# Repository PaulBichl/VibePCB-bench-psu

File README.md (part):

# vibepcb-bench-psu

USB-C PD (20 V) powered bench supply, 2 independent channels, 1.6-16.6 V / 3 A each, constant voltage / constant
current, designed with [VibePCB](../VibePCB). Board: `boards/bench-psu` (rev C: 90 x 60 mm, 4 layers, parts on both
sides). Design rationale is also in the header of `boards/bench-psu/index.circuit.tsx`.

The board is the front panel: the top carries what a user touches (0.96" OLED module, per channel an encoder and an
ON/OFF button, ON / CC LEDs, the output terminal), the bottom carries all electronics.

```
USB-C PD (STUSB4500, 20 V) -> P-FET -> VIN
   VIN -> 5 V buck (LMR33630) -> 3.3 V LDO -> ESP32-S3-MINI-1 (I2C, PWM, PCNT, ADC, BLE, native USB)
   VIN -> LMR33630 buck (x2) -> 20 mR shunt (INA226 + INA181) -> output terminal (CH1, CH2)
ESP32 PWM -> RC -> op-amp/NPN current sink on FB            = voltage set point (CV)
ESP32 PWM -> RC -> differential PI integrator -> diode -> FB = current limit (CC), vs INA181 (1 V/A)
INA226 ALERT -> buck EN = hardware over-current trip (backstop)
per channel: EC11 encoder (turn: set, push: V <-> I), ON/OFF button, ON LED (= EN), CC LED (GPIO),
             output discharge (2N7002 + 4.7k while off), SS54 reverse diode, FB clamp, NTC on the converter
USB D+/D-: 90 Ohm pair on the top layer (USBLC6 -> ESP32)
J3: SSD1306 0.96" I2C OLED module (bought separately, see "Parts bought separately")
```

## Look at it (`boards/bench-psu/hardware/`)

| What | File |
|------|------|
| Schematic | [bench-psu-schematic.pdf](boards/bench-psu/hardware/bench-psu-schematic.pdf) |
| Top view (3D) | [bench-psu-top.png](boards/bench-psu/hardware/bench-psu-top.png) |
| Bottom view (3D) | [bench-psu-bottom.png](boards/bench-psu/hardware/bench-psu-bottom.png) |
| Layout | [front](boards/bench-psu/hardware/bench-psu-layout-front.svg), [back](boards/bench-psu/hardware/bench-psu-layout-back.svg), [PDF](boards/bench-psu/hardware/bench-psu-layout.pdf) |
| KiCad project (open the `.kicad_pro`) | [kicad/](boards/bench-psu/hardware/kicad/) |
| BOM (JLCPCB format, LCSC + MPN) | [bench-psu-bom.csv](boards/bench-psu/hardware/bench-psu-bom.csv) |

Fab files (Gerbers + drill, BOM, CPL, bring-up sheet, firmware pin header) are generated, not committed:
`hatch run pcb fab bench-psu` writes them to `out/bench-psu/fab/` (it refuses unless `check --strict` passes).

## Design decisions

- **Parts:** everything in LCSC stock (checked 2026-10-25 with `hatch run pcb cost bench-psu`); basic-library passives
  wherever the value exists. Two-sided assembly: all SMD on the bottom except the status LEDs and their drivers;
  the front-panel parts (encoders, buttons, OLED header, terminal) are through-hole and hand-soldered.
- **Form factor:** 90 x 60 mm: the front-panel parts are through-hole, so their pins also take
  room on the bottom; 90 mm is what the two channel blocks, the control columns and the ESP32 need side by side.
  4 x M3 holes at (+-41.5, +-26.5) mm from the centre, keepouts for screw heads in `vibepcb.toml`.
- **Plain buck, not buck-boost:** the PD input (20 V) is always above the output (max 16.6 V).
- **Converter:** LMR33630A per channel (synchronous, 3 A, 400 kHz, HSOIC-8 with exposed pad, 36 V input),
  15 uH / 7 A sat FXL1040-150 inductor (TI's L_MIN is 11.6 uH at 16.6 V / 400 kHz), 4 x 22 uF/25 V ceramic output +
  100 uF electrolytic at the terminal (C25 / C26: the ceramics derate to ~18 uF at 16 V while the loop gain stays the
  same), 2 x 10 uF/50 V + 220 nF/50 V input.
  **Thermal vias** (2 x 3, 0.3 mm, `[thermal_vias.*]`) in every LMR33630 exposed pad; the pad connects solid to the
  pours.
- **Voltage setting, fail-safe:** an op-amp (TLV9062) + NPN sinks Ic = Vc / 2.2k from the feedback node,
  Vc = PWM (14-bit, 2-pole RC) * 10k/120k (R106 + R107 + R108): Vout = 1.6 V + 4.55 * Vpwm, i.e. 1.6 V at 0 V / floating PWM or MCU reset,
  16.6 V at 3.3 V PWM (the hardware maximum), ~0.9 mV per step. Feedback is taken at the terminal, after the shunt.
  Firmware closes the loop on the INA226 bus-voltage reading.
- **Loop compensation:** the FB network has a feedback gain of 0.625 at every output voltage, but the LMR33630's
  internal compensation expects 1 V / Vout: unstable without help. 6.8k + 220 nF from FB to GND (lag network) lowers
  the gain above ~100 Hz: phase margin 93-98 deg, crossover 9-38 kHz (simulated; see the open point on the lowest
  phase below crossover in "Status").
- **FB clamp (rev C, from the review):** the buck can't pull its output down, so after a set-point drop or a lost PWM
  (MCU reset) FB would sit at 0.625 x OUT, up to 10.4 V against a 5.5 V absolute maximum, for seconds. A 1N4148W per
  channel (D16 / D26, FB -> 3V3) holds it at ~3.8 V (`sim/powerup_ch.cir`); in operation it is reverse-biased (nA).
- **Start-up:** the lag capacitor is pre-charged to ~1.3 V while the channel is off (1N4148W + 100k from the
  discharge-gate node); otherwise the soft start charges it through the 120k top resistor and every enable overshoots
  to ~7.7 V. With EN high the diode blocks: no offset. Overshoot 0.02 % (`sim/powerup_ch.cir`).
- **Constant current:** INA181A2 (x50) on the shunt = 1 V/A; ISET = PWM, 2-pole RC, 1 V/A; a TLV9062 half as a
  differential PI integrator (10k, 330 R + 100 nF in both legs) sources current into FB through 10k + 1N4148W when
  I > Iset. Differential, because the plant gain into a short is ~240: a plain non-inverting PI keeps a
  high-frequency gain >= 1 and oscillates. Simulated phase margin >= 91 deg from a short to 5 R, a 20 R -> 2 R step
  settles in 1.7 ms (`sim/cc_loop.cir`). In CV the amp rests at 0 V, the diode is off. Into a hard short the
  converter may hiccup once before the loop holds (current limited either way).
- **Enable / current trip:** ESP32 drives each buck's EN through 10k (100k pull-down: off at reset). The INA226 ALERT
  (shunt over-limit, latched) pulls EN low directly: the hard backstop, at a ceiling the firmware sets above Iset.
- **Output:** 100 nF at the terminal (INA226 VBUS); SS54 reverse diode (a reversed source is clamped); active
  discharge while off (2N7002 + 4.7k, gate from 5 V, held off by an NPN while EN is high): "off" is below 0.5 V within
  ~2 s (~60 s through the divider alone), also at reset and after a trip.
- **Cooling: passive.** ~2-2.5 W per channel at 3 A (1.2-1.6 W in the IC, datasheet-maximum Rds(on)). With the thermal
  vias Tj stays below 112 C at 45 C ambient (35 C room + 10 K in a vented enclosure; ~160 C without vias,
  `sim/buck_loadpoints.cir`). A 10k NTC
  (Murata NCP18XH103F03RB) next to each converter feeds ESP32 ADC1 (IO1 / IO2) for firmware derating; the converter's
  thermal shutdown is the last resort. No fan.
- **Measurement:** INA226 per channel (0x40 CH1, 0x41 CH2), 20 mR shunt: 4.096 A full scale, 125 uA / 1.25 mV LSB,
  60 mV drop and 0.18 W at 3 A.
- **Input protection:** ESDA25P35 TVS on VBUS at the connector (ahead of Q1: the STUSB4500's VDD is rated 28 V),
  ESDA25W ESD array on CC1 / CC2 as in ST's reference; D+/D- through the USBLC6. The connector shell goes to GND
  through 1 MOhm || 4.7 nF rated 1 kV (an 8 kV / 150 pF shell discharge charges it to ~250 V).
- **USB data:** D+/D- run from the USBLC6 to the ESP32 as a coupled pair on the top layer over the In1 GND plane,
  0.32 / 0.2 mm = 90 Ohm differential (JLC04161H-7628 stack-up), two vias per line; drawn as a fixed path in the TSX
  (tscircuit's router does not couple pairs). Full Speed USB would work uncoupled too; this is the standard layout.
- **Input:** STUSB4500 drives the AO4407A gate through 47k against 100k gate-source (Vgs stays inside +-25 V up to the
  TVS clamp), 100 nF gate-source for a slow turn-on. SMBJ22A TVS (35.5 V clamp, below the LMR33630's 38 V abs max),
  100 uF SMD electrolytic for damping.
- **Logic supply:** 5 V buck (same LMR33630, 6.8 uH / 4 A sat FXL0530, 4 x 22 uF output, two of them on the top side)
  -> AP2112K 3.3 V; native USB on the ESP32 for flashing / CDC.
- **Front panel:** EC11E15244B2 encoders (counted by the S3's PCNT units), Omron B3F-4055 12 mm buttons (wired on
  diagonal pads 1 / 4: always across the contact), 3.3k pull-up + 33 nF on every front-panel line (1 mA contact
  current, the EC11's minimum for contact wetting). 0.96" SSD1306
  I2C module (0x3C) on J3, its content is firmware.
- **Status LEDs:** ON (yellow-green) follows the converter's EN node through an NPN (hardware truth, dark after an
  INA226 trip); CC (red) is a GPIO (IO21 / IO47) the firmware lights while the channel is current-limited.
- **Antenna:** the ESP32-S3-MINI-1 (bottom) points its antenna at the +x board edge; no copper under it on any layer.

## History

Rev A (first draft) used a TSOT-23 converter at 1.1 MHz, injected the PWM straight into FB (0 V PWM = 18 V out) and had
no hardware current trip. Rev B moved to the LMR33630 with the fail-safe current-sink voltage setting, the INA226 trip
and the FB lag network. Rev C (this board):

| rev B | rev C | why |
|-------|-------|-----|
| 90 x 76 mm, everything on top | 90 x 60 mm, front panel on top, electronics on the bottom | the board is the front panel; smaller |
| OLED + KY-040 encoder as modules on headers | OLED module on J3, per channel EC11 encoder + ON/OFF button on the board | per-channel controls |
| current trip only (INA226 ALERT -> EN) | CC loop (INA181 + differential PI into FB) + the trip as backstop | a real current limit instead of switching off |
| lag capacitor starts discharged | pre-charged while off (1N4148W + 100k) | 7.7 V overshoot at every enable (simulated) |
| output decays over ~28 s when off | 2N7002 + 4.7k discharge while EN is low | "off" means 0 V |
| no reverse protection | SS54 across each output | reversed source / battery clamped |
| no thermal vias | 2 x 3 via grid in each exposed pad | Tj ~160 C -> 112 C at 45 C ambient, 3 A |
| no temperature sensing, no mounting holes | NTC per converter on ADC1, 4 x M3 | firmware derating with passive cooling; enclosure |
| sim decks run by hand | 5 decks run by `check`, pass ranges with sources | verification is enforced |
| 2.4k sink resistor: Vout_max 15.2 V | 2.2k: 16.6 V | review: R106 in series with the VSET divider |
| 10 uH channel / 15 uH (1.65 A sat) logic inductors | 15 uH / 7 A sat, 6.8 uH / 4 A sat | below TI's L_MIN; saturating below the current limit (review) |
| no TVS / ESD at the USB-C input, 50 V shell cap | ESDA25P35 on VBUS, ESDA25W on CC, 1 kV shell cap | hot-plug and shell ESD (review) |
| ceramics only on the outputs | + 100 uF per output | ceramic capacitance collapses at 16 V (review) |
| FB unprotected | FB clamp to 3V3 | FB at 10.4 V after a set-point drop (review) |
| 10k / 10 nF front-panel lines | 3.3k / 33 nF | encoder contacts below their 1 mA wetting current (review) |
| D+/D- auto-routed | 90 Ohm pair on the top layer | standard USB layout |

## Simulations (`boards/bench-psu/sim/`, run by `hatch run pcb check`)

Each deck declares what it proves (`* covers:`) and its pass ranges with their source (`* range:`, datasheet /
intent / house defaults); `check` runs ngspice, compares the deck's R/C values with the board and judges the results.

| Deck | Covers | Result |
|------|--------|--------|
| `buck_loop.cir` | CV loop U11 / U21 | phase margin 93-98 deg at crossover (1.6-16 V; >= 63 deg for C25/C26 ESR 0.05..1 Ohm), 2 A step <= 251 mV (intent: 400 mV) |
| `cc_loop.cir` | CC loop | phase margin >= 91 deg (short .. 5 R), settles in 1.7 ms, current error < 0.01 % |
| `powerup_ch.cir` | power-up U11 / U21 | overshoot 0.02 %, settles 13.5 ms after EN, 16.60 V at full PWM, FB <= 3.8 V after a set-point drop |
| `powerup_logic.cir` | power-up U3 / U4 | V5 5.15-5.17 V, V3V3 3.28-3.30 V through a 0.1 -> 0.35 A step |
| `buck_loadpoints.cir` | thermal U11 / U21 | Tj <= 112 C at 45 C ambient (max Rds(on)), inductor peak <= 3.41 A (ISC min 3.85 A) |

Models: averaged peak-current-mode buck with the LMR33630's internal compensation *derived* (not published), COMP
clamp, PFM (no reverse current); switching-level power stage for the load points. Plots and tables:
[sim/README.md](boards/bench-psu/sim/README.md).

## Design review (reviewer agent)

`hatch run pcb review bench-psu --run`: a fresh Claude session, with no access to the design conversation, checks every
part against its datasheet (answers and citations in `boards/bench-psu/review.toml`). Issues get fixed or accepted with
a written reason in `boards/bench-psu/findings.toml`; `check --strict` (needed by `fab`) fails while any is open.

| Round | Items | ok / issue / unknown | Notable catch, and what happened |
|------:|------:|---------------------:|----------------------------------|
| 1 | 178 | 155 / 15 / 8 | max output 15.2 V, not 16.6 V; both inductors too small; no input TVS / ESD - fixed |
| 2 | 185 | 169 / 11 / 5 | output capacitance collapses at 16 V; 100 nF instead of 220 nF HF input caps - fixed |
| 3 | 185 | 171 / 5 / 9 | encoder contacts below their wetting current - fixed |
| 4 | 185 | 171 / 6 / 8 | FB pin over-voltage after a set-point drop - fixed (clamp) |
| 5 | 189 | 176 / 5 / 8 | USB shell capacitor rated 50 V - fixed (1 kV) |
| 6 | 189 | 182 / 4 / 3 | hiccup into a hard short - intent corrected, bring-up test |

Accepted with reasons (see `findings.toml`): L1's 4 A soft saturation on the internal 5 V rail, Q1 gate drive on a 5 V-only
source, the 3 A channel budget at the converter's rating (firmware caps ISET at 3.0 A), J1 at its 3 A rating, LED / TVS
polarity and the ESP32's corner GND pads (verified on the footprint), the OLED module pin order (checked at bring-up),
and the loop stability (rests on unpublished compensation constants: measured on the prototype).

## Pin map (ESP32-S3)

| Pin | Net | Use |
|-----|-----|-----|
| IO8 / IO9 | I2C_SDA / I2C_SCL | STUSB4500 0x28, INA226 0x40 / 0x41, OLED 0x3C (4.7k pull-ups) |
| IO10 | PD_ALERT | STUSB4500 alert (10k pull-up) |
| IO4 / IO5 | PWM1 / PWM2 | voltage set point CH1 / CH2 |
| IO11 / IO12 | ISET1 / ISET2 | current limit CH1 / CH2 (1 V/A after the RC) |
| IO6 / IO7 | EN1_MCU / EN2_MCU | channel enable (through 10k; INA226 ALERT overrides) |
| IO1 / IO2 | NTC1 / NTC2 | converter temperature (ADC1; 10k to 3V3, NTC to GND) |
| IO15 / IO16 / IO17 | ENC1_A / ENC1_B / ENC1_SW | CH1 encoder |
| IO13 / IO14 / IO18 | ENC2_A / ENC2_B / ENC2_SW | CH2 encoder |
| IO38 / IO39 | BTN1 / BTN2 | ON/OFF buttons (low = pressed) |
| IO21 / IO47 | LED_CC1 / LED_CC2 | red CC LED CH1 / CH2 (high = on) |
| IO19 / IO20 | USB_DN / USB_DP | native USB |
| IO0, EN | BOOT, EN_RST | tactile switches (bottom) |

`hatch run pcb fab bench-psu` also writes `bench-psu-pins.h` (net -> pin defines) for the firmware.

## Firmware duties (not part of this repo yet)

- Write the STUSB4500 NVM once over I2C (20 V / 3 A). The factory NVM already asks a 20 V source for 20 V / 1 A
  (PDO3, DS12499 table 18): keep both channels off until the NVM is written.
- **Enable sequence:** PWM (VSET) = 0 before EN high, wait ~5 ms for the soft start, then ramp the set point (>= 5 ms).
  Enabling at a high set point starts at the converter's current limit with no soft start (`sim/powerup_ch.cir`).
- Close the voltage loop on the INA226 bus-voltage reading (PWM -> Vout is ~4.55 V/V, offset trimmed per channel).
- Current limit: ISET PWM = Iset * 1 V/A, capped at 3.0 A (ISET full scale would be 3.3 A; the LMR33630 is rated 3 A); light the CC LED while the INA226 current is within ~2 % of Iset.
  Program each INA226's shunt over-limit (Mask/Enable SOL + LEN latch) to a ceiling above Iset (e.g. Iset + 0.5 A,
  max 3.5 A); after a trip read Mask/Enable (clears the latch) and report it.
- Temperature: NTC (B 3380) -> derate the current limit above ~85 C board temperature, switch off above ~100 C.
- Budget power: the sum of both channels stays inside the negotiated PDO (60 W at 20 V / 3 A).
- UI: encoders via PCNT, push toggles V / I editing; ON/OFF buttons toggle EN; the OLED shows set and measured V / I,
  CV / CC and temperature per channel.

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
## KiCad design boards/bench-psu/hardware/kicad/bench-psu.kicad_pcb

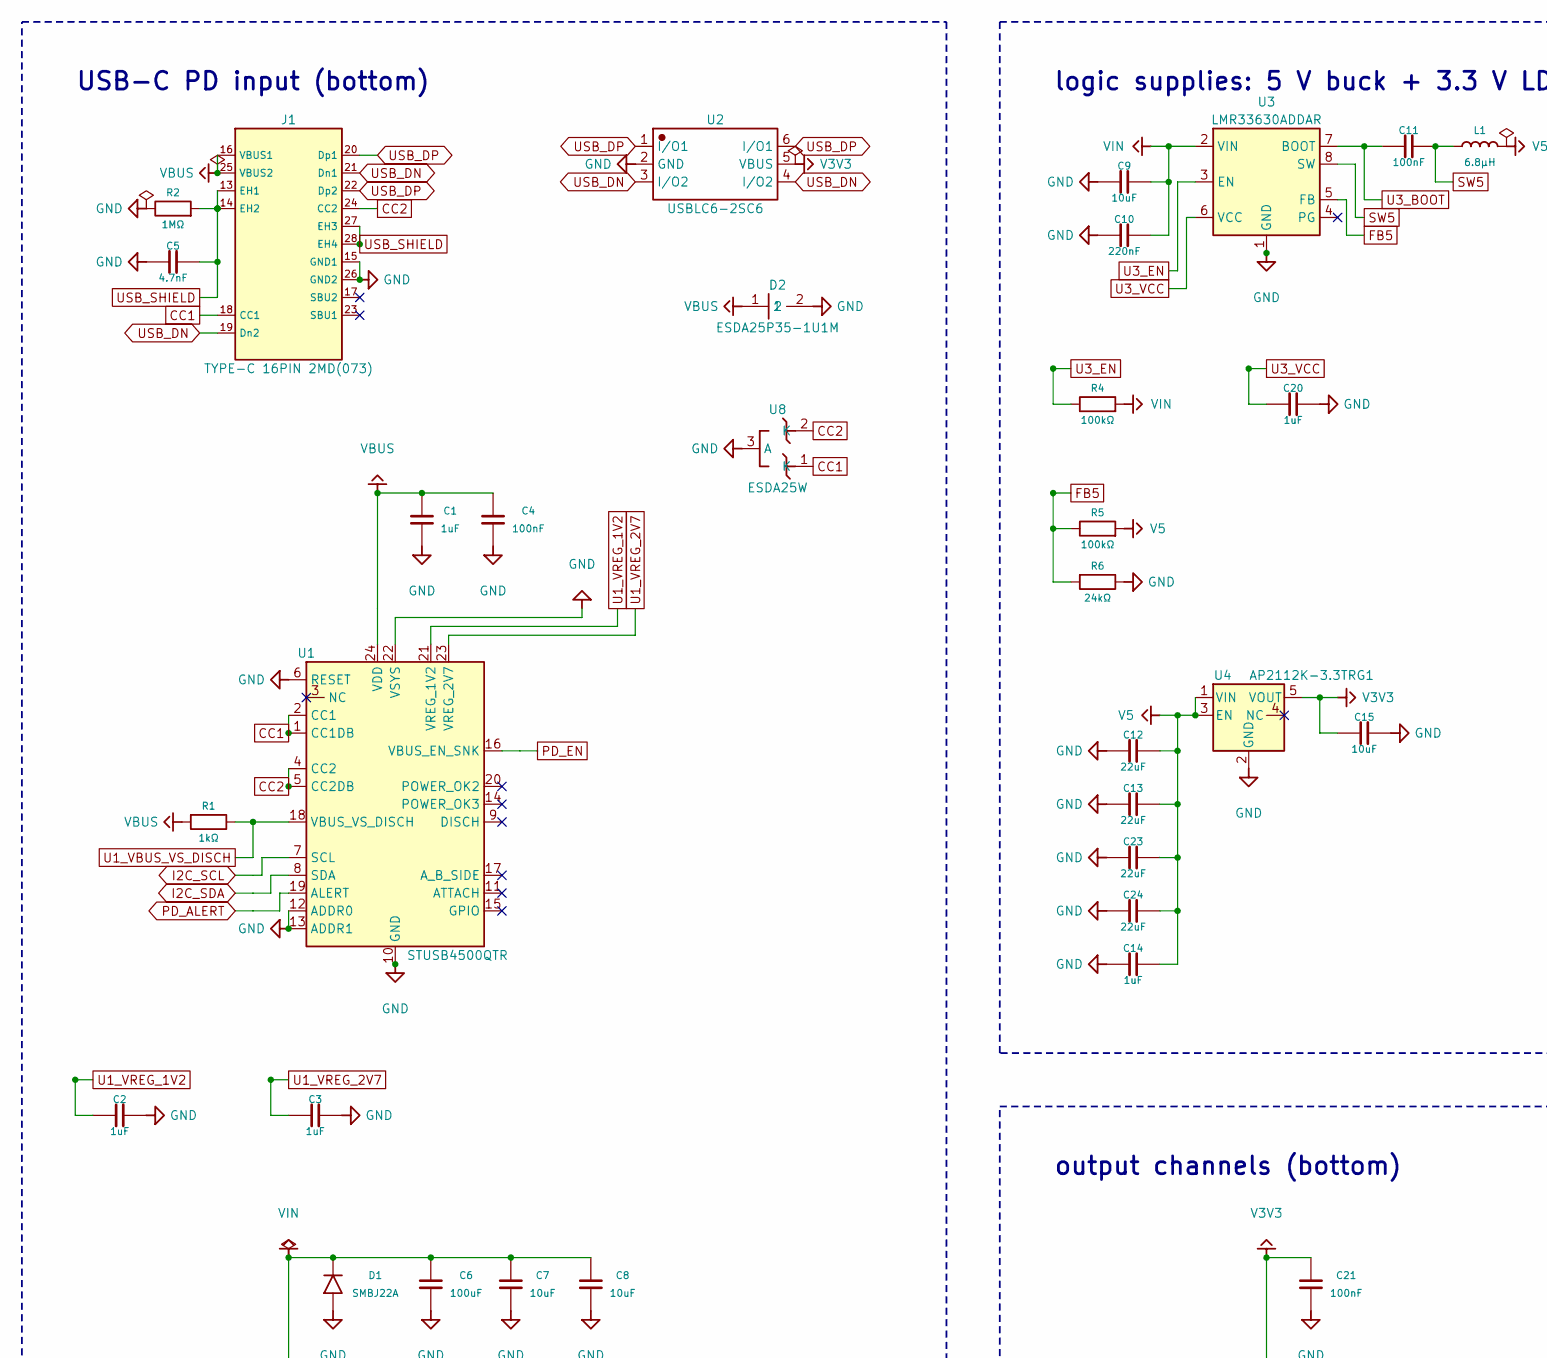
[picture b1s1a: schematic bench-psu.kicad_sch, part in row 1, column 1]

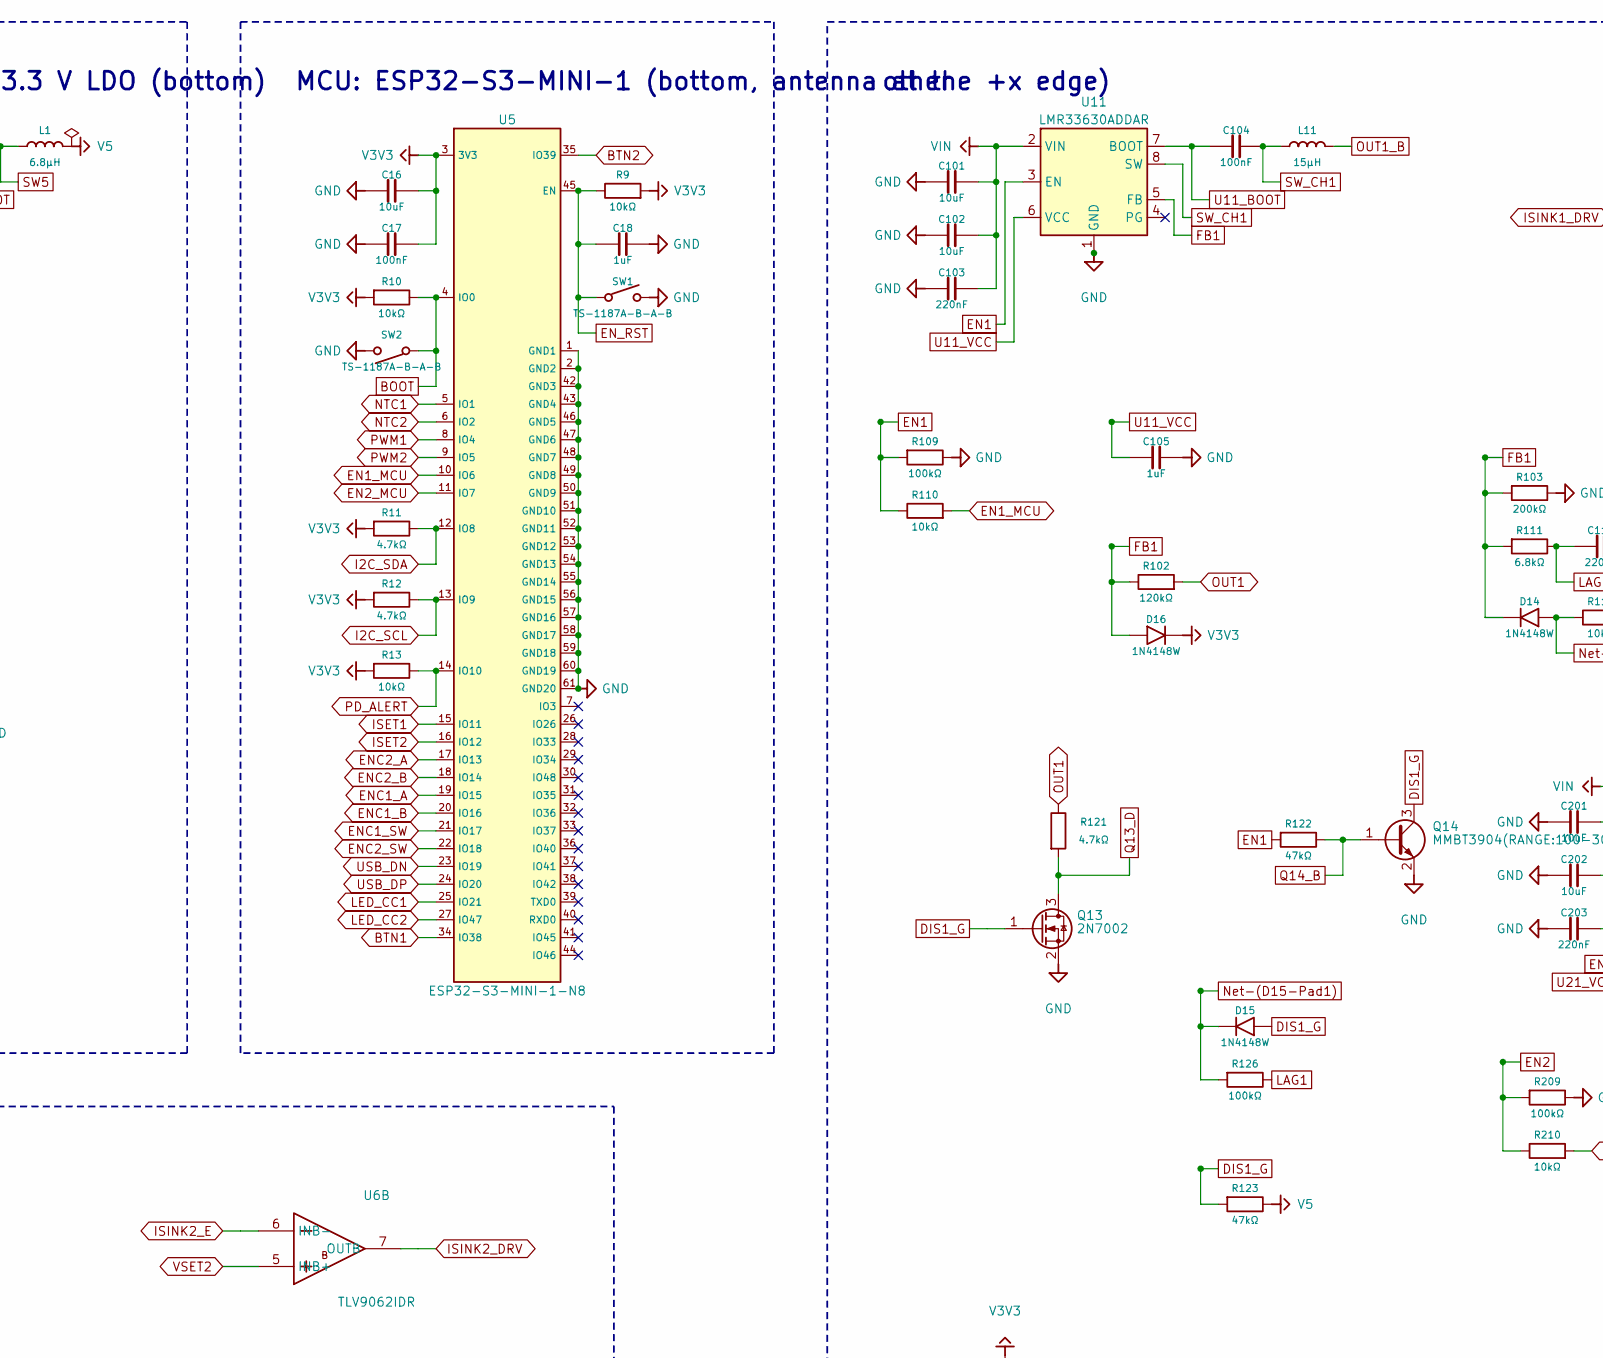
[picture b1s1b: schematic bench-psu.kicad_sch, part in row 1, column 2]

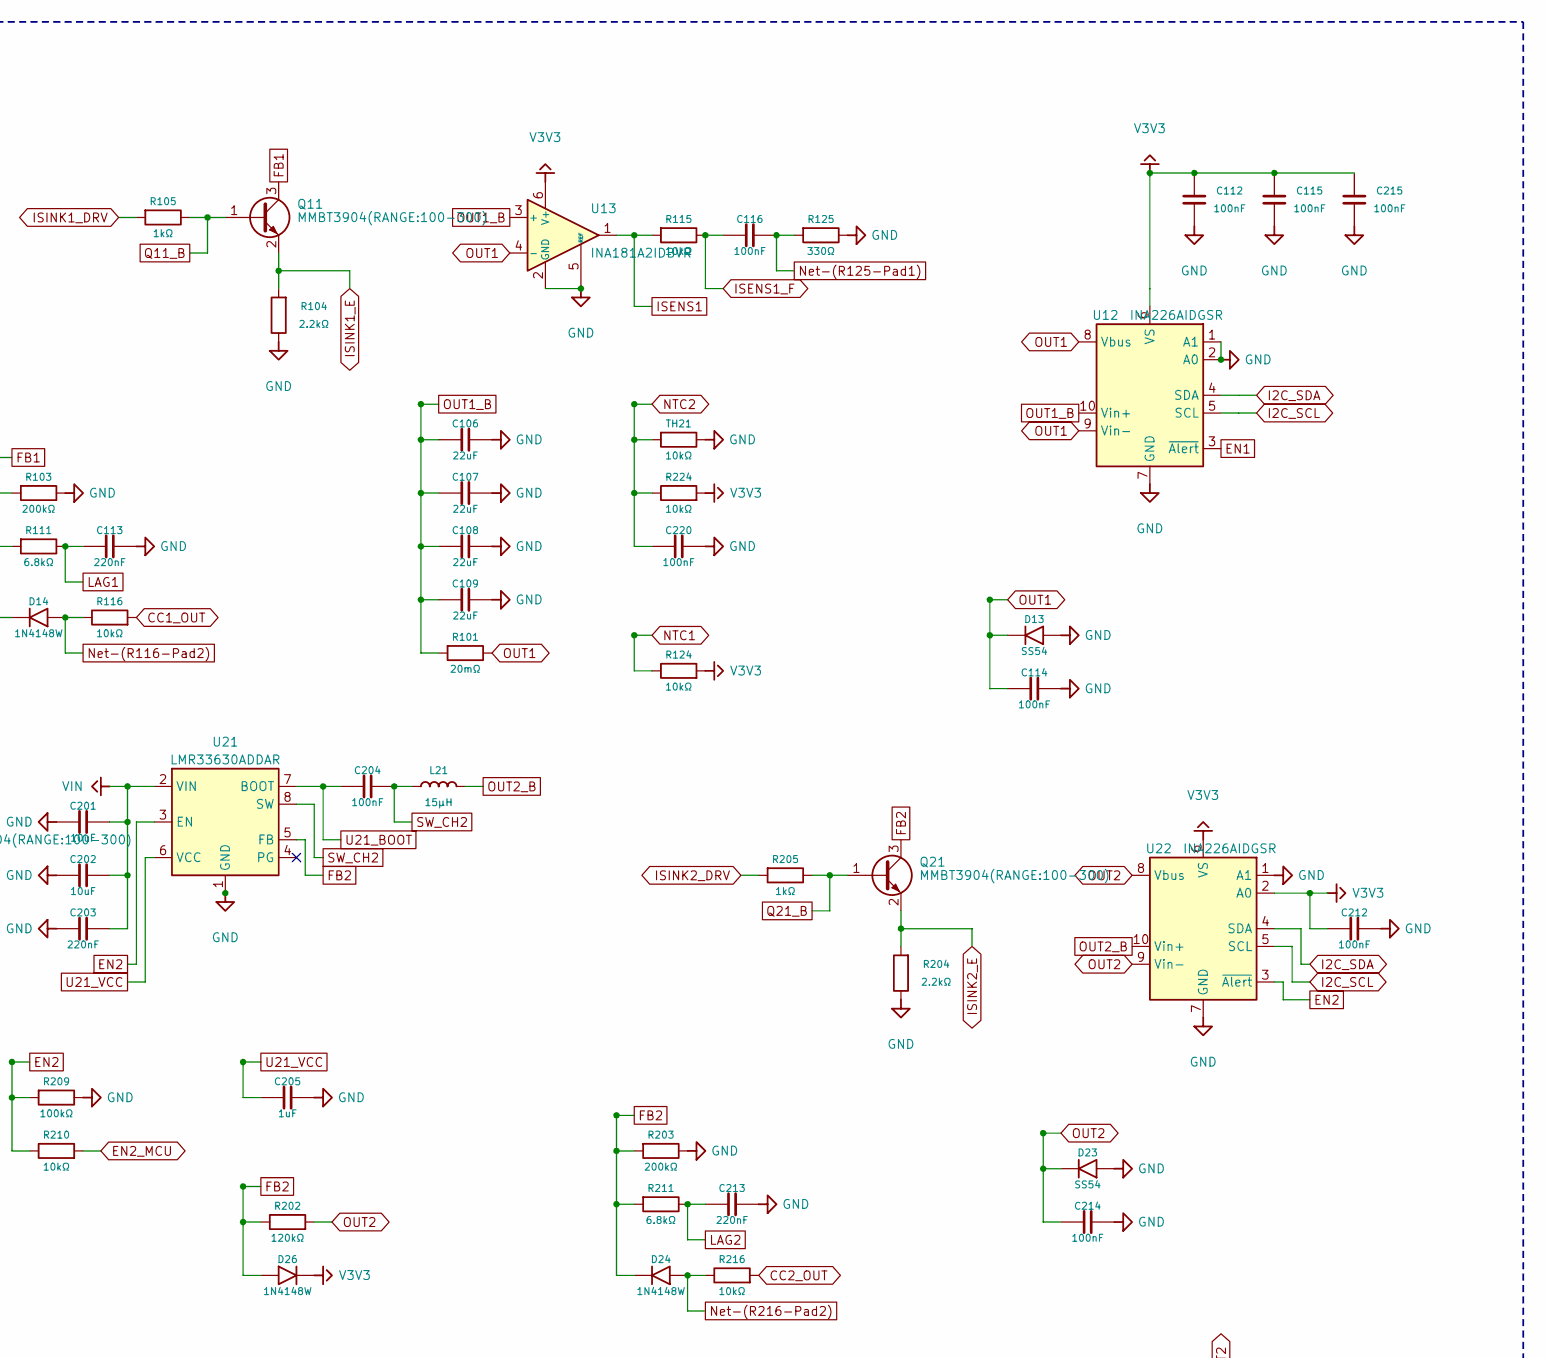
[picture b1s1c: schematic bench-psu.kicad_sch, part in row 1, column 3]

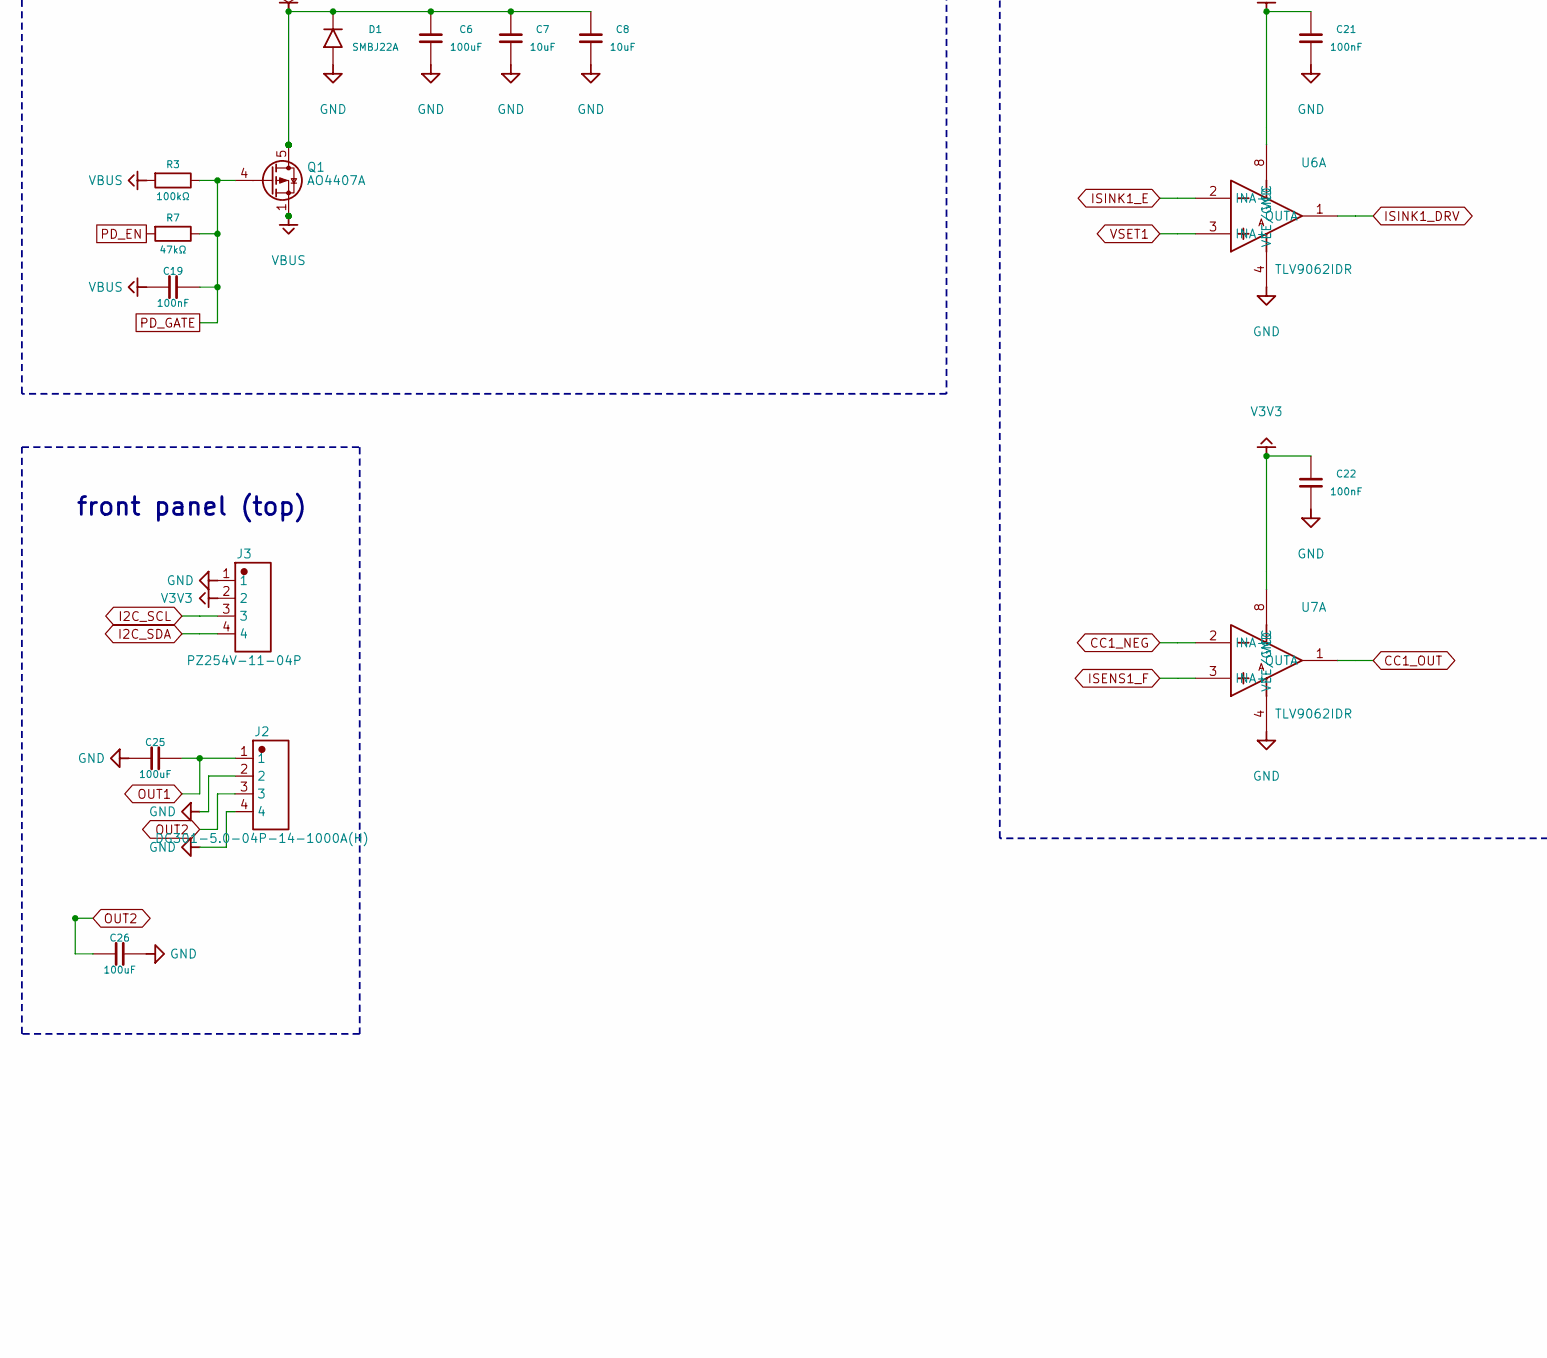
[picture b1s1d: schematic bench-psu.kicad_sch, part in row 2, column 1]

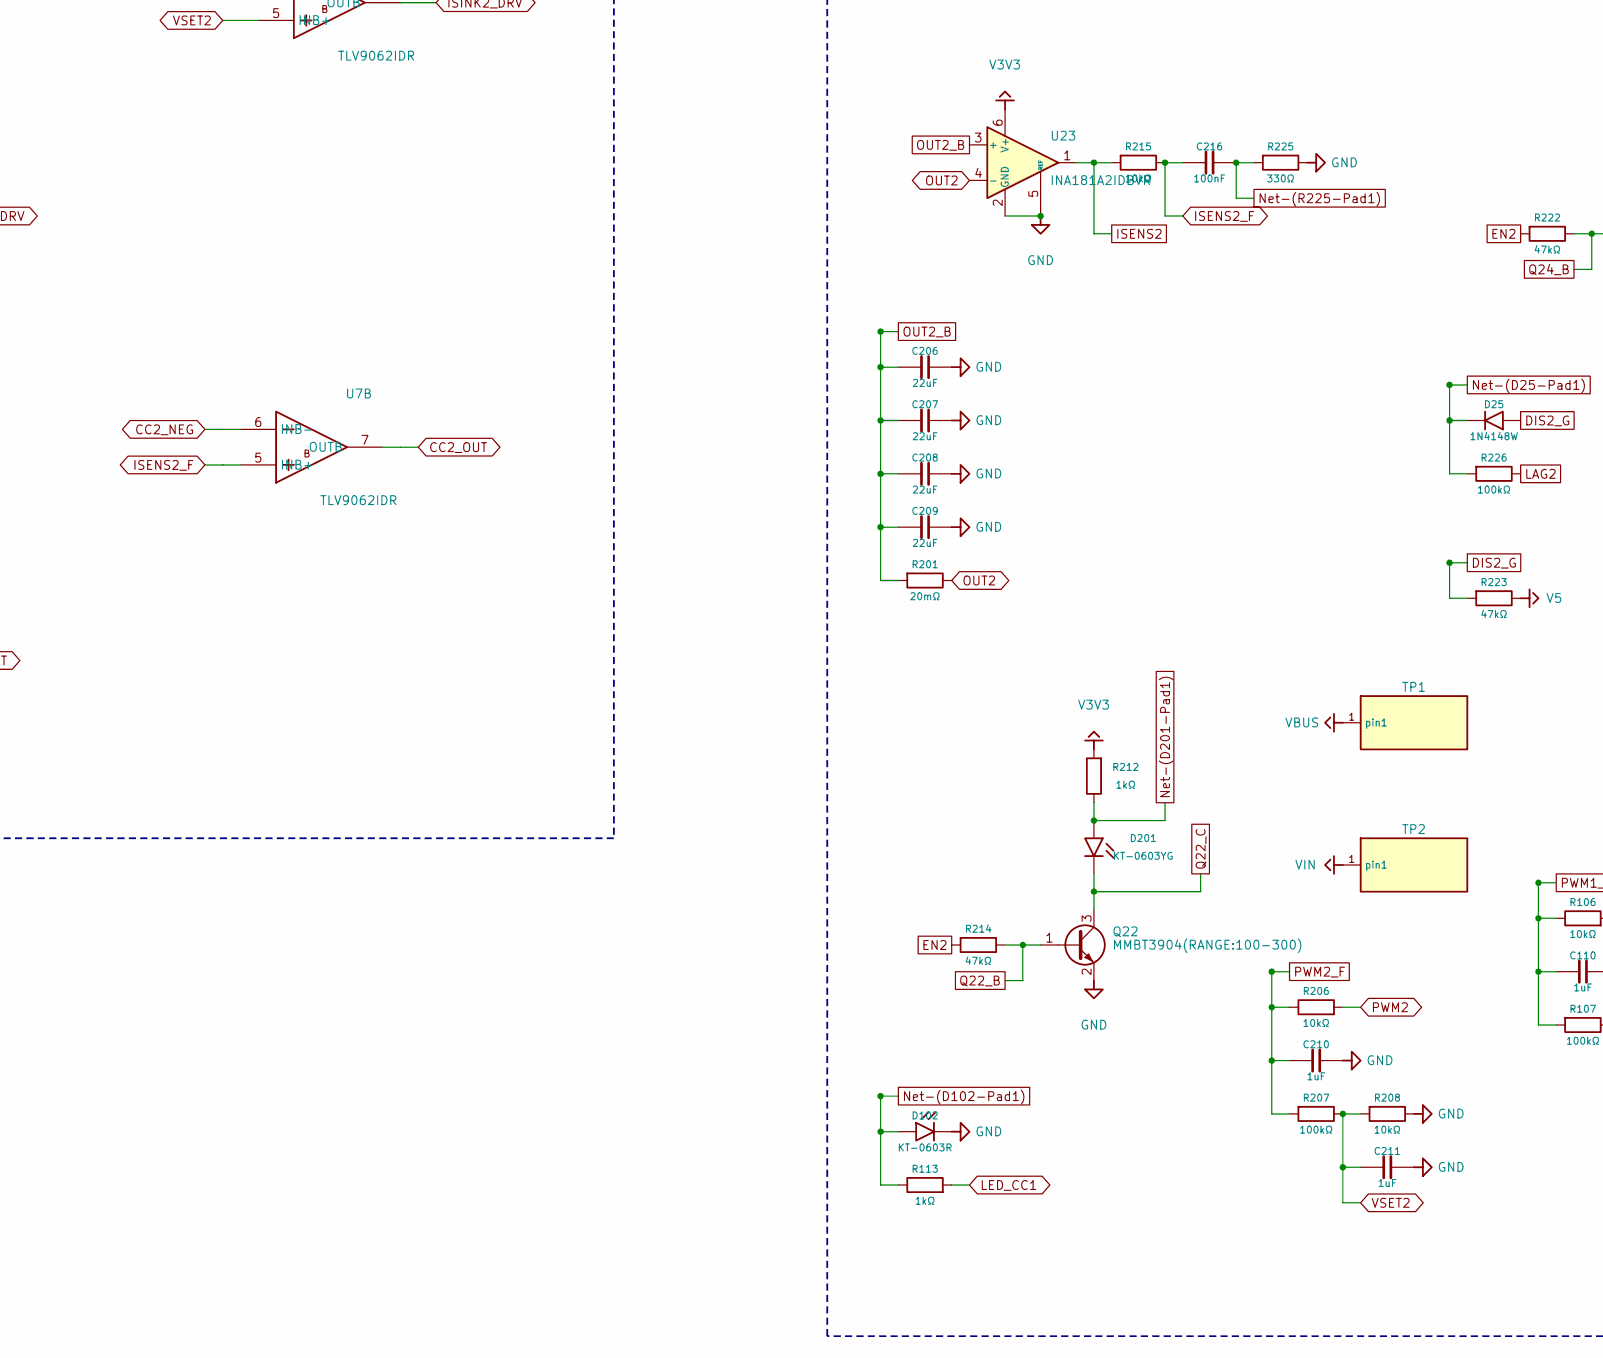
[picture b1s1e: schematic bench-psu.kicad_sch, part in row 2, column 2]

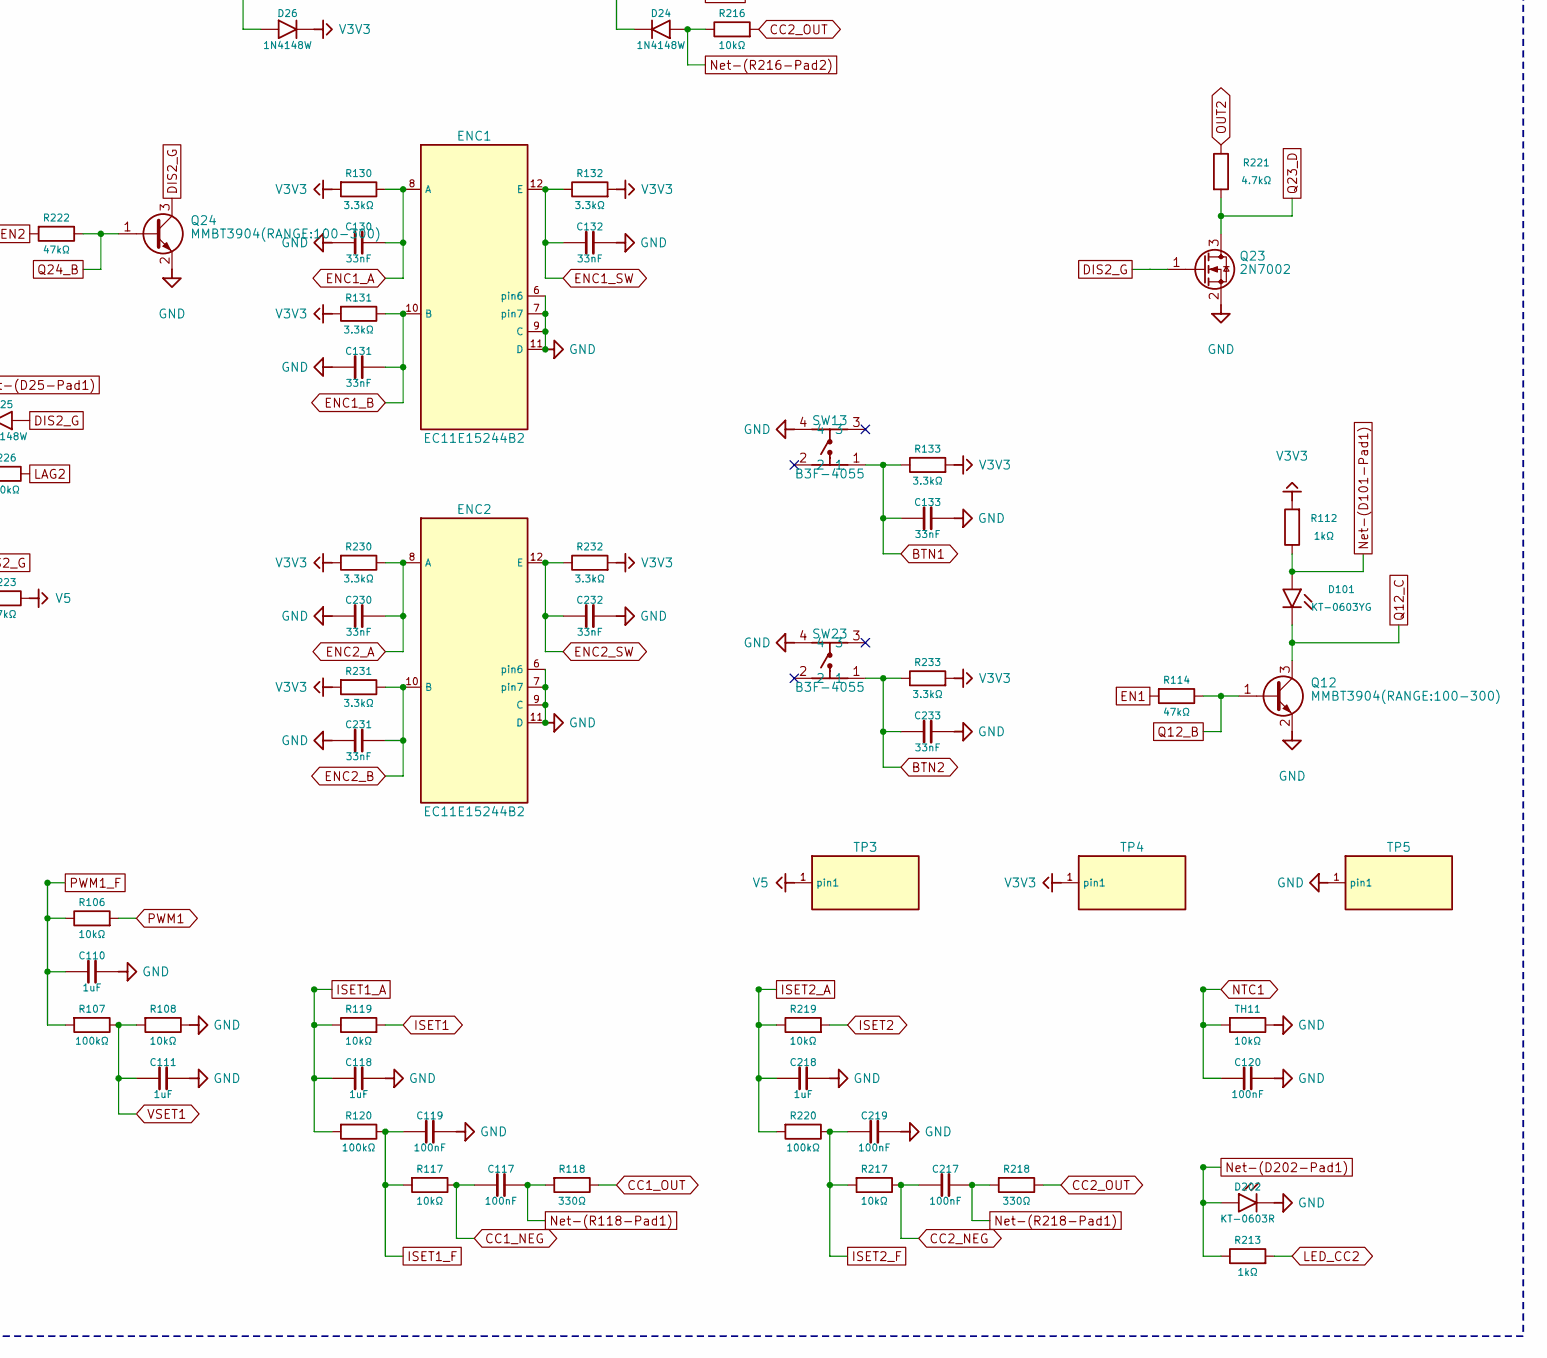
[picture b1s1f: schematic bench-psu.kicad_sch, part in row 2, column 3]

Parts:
C1, C2, C3, C14, C18, C20, C105, C110, C111, C118, C205, C210, C211, C218: 1uF; capacitor_cap0603; LCSC C15849
C4, C11, C17, C19, C21, C22, C104, C112, C114, C115, C116, C117, C119, C120, C204, C212, C214, C215, C216, C217, C219, C220: 100nF; capacitor_cap0603; LCSC C14663
C5: 4.7nF; capacitor_cap0805; LCSC C565695
C6, C25, C26: 100uF; RVT1V101M0607_100UF_35V; MPN RVT1V101M0607 100UF 35V; LCSC C970686
C7, C8, C9, C101, C102, C201, C202: 10uF; capacitor_cap1206; LCSC C13585
C10, C103, C203: 220nF; capacitor_cap0603; LCSC C107083
C12, C13: 22uF; capacitor_cap0805; LCSC C45783
C15, C16: 10uF; capacitor_cap0805; LCSC C15850
C23, C24, C106, C107, C108, C109, C206, C207, C208, C209: 22uF; capacitor_cap1206; LCSC C12891
C113, C213: 220nF; capacitor_cap0603; LCSC C21120
C130, C131, C132, C133, C230, C231, C232, C233: 33nF; capacitor_cap0603; LCSC C21117
D1: SMBJ22A; MPN SMBJ22A; LCSC C151920
D2: ESDA25P35-1U1M; MPN ESDA25P35-1U1M; LCSC C1974707
D13, D23: SS54; MPN SS54; LCSC C22452
D14, D15, D16, D24, D25, D26: 1N4148W; MPN 1N4148W; LCSC C81598
D101, D201: KT-0603YG; MPN KT-0603YG; LCSC C2289
D102, D202: KT-0603R; MPN KT-0603R; LCSC C2286
ENC1, ENC2: EC11E15244B2; MPN EC11E15244B2; LCSC C470754
J1: TYPE-C 16PIN 2MD(073); TYPE-C_16PIN_2MD_073; MPN TYPE-C 16PIN 2MD(073); LCSC C2765186
J2: DG301-5.0-04P-14-1000A(H); DG301-5_0-04P-14-1000A_H; MPN DG301-5.0-04P-14-1000A(H); LCSC C3037697
J3: PZ254V-11-04P; MPN PZ254V-11-04P; LCSC C492403
L1: 6.8µH; FXL0530-6R8-M; MPN FXL0530-6R8-M; LCSC C177249
L11, L21: 15µH; FXL1040-150-M; MPN FXL1040-150-M; LCSC C475916
Q1: AO4407A; MPN AO4407A; LCSC C2841482
Q11, Q12, Q14, Q21, Q22, Q24: MMBT3904(RANGE:100-300); MMBT3904_RANGE_100-300; MPN MMBT3904(RANGE:100-300); LCSC C20526
Q13, Q23: 2N7002; MPN 2N7002; LCSC C8545
R1, R105, R112, R113, R205, R212, R213: 1kΩ; resistor_res0603; LCSC C21190
R2: 1MΩ; resistor_res0603; LCSC C22935
R3, R4, R5, R107, R109, R120, R126, R207, R209, R220, R226: 100kΩ; resistor_res0603; LCSC C25803
R6: 24kΩ; resistor_res0603; LCSC C23352
R7, R114, R122, R123, R214, R222, R223: 47kΩ; resistor_res0603; LCSC C25819
R9, R10, R13, R106, R108, R110, R115, R116, R117, R119, R124, R206, R208, R210, R215, R216, R217, R219, R224: 10kΩ; resistor_res0603; LCSC C25804
R11, R12, R121, R221: 4.7kΩ; resistor_res0603; LCSC C23162
R101, R201: 20mΩ; resistor_res2512; LCSC C105360
R102, R202: 120kΩ; resistor_res0603; LCSC C25808
R103, R203: 200kΩ; resistor_res0603; LCSC C25811
R104, R204: 2.2kΩ; resistor_res0603; LCSC C4190
R111, R211: 6.8kΩ; resistor_res0603; LCSC C23212
R118, R125, R218, R225: 330Ω; resistor_res0603; LCSC C23138
R130, R131, R132, R133, R230, R231, R232, R233: 3.3kΩ; resistor_res0603; LCSC C22978
SW1, SW2: TS-1187A-B-A-B; MPN TS-1187A-B-A-B; LCSC C318884
SW13, SW23: B3F-4055; MPN B3F-4055; LCSC C84931
TH11, TH21: 10kΩ; NCP18XH103F03RB; MPN NCP18XH103F03RB; LCSC C13564
TP1, TP2, TP3, TP4, TP5: test_point_smtpad_circle_d1
U1: STUSB4500QTR; MPN STUSB4500QTR; LCSC C2678061
U2: USBLC6-2SC6; MPN USBLC6-2SC6; LCSC C2687116
U3, U11, U21: LMR33630ADDAR; MPN LMR33630ADDAR; LCSC C841384
U4: AP2112K-3.3TRG1; AP2112K-3_3TRG1; MPN AP2112K-3.3TRG1; LCSC C51118
U5: ESP32-S3-MINI-1-N8; MPN ESP32-S3-MINI-1-N8; LCSC C2913206
U6, U7: TLV9062IDR; MPN TLV9062IDR; LCSC C398355
U8: ESDA25W; MPN ESDA25W; LCSC C2935152
U12, U22: INA226AIDGSR; MPN INA226AIDGSR; LCSC C49851
U13, U23: INA181A2IDBVR; MPN INA181A2IDBVR; LCSC C2058784

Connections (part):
BOOT: R10.2, SW2.1 (AB), U5.4 (IO0)
BTN1: C133.1, R133.2, SW13.1, U5.34 (IO38)
BTN2: C233.1, R233.2, SW23.1, U5.35 (IO39)
CC1: J1.18 (CC1), U1.1 (CC1DB), U1.2 (CC1), U8.1 (K)
CC1_NEG: C117.1, R117.2, U7.2 (INA-)
CC1_OUT: R116.1, R118.2, U7.1 (OUTA)
CC2: J1.24 (CC2), U1.4 (CC2), U1.5 (CC2DB), U8.2 (K)
CC2_NEG: C217.1, R217.2, U7.6 (INB-)
CC2_OUT: R216.1, R218.2, U7.7 (OUTB)
DIS1_G: D15.2 (anode), Q13.1 (G), Q14.3 (C), R123.1
DIS2_G: D25.2 (anode), Q23.1 (G), Q24.3 (C), R223.1
EN1: R109.1, R110.2, R114.1, R122.1, U11.3 (EN), U12.3 (~Alert)
EN1_MCU: R110.1, U5.10 (IO6)
EN2: R209.1, R210.2, R214.1, R222.1, U21.3 (EN), U22.3 (~Alert)
EN2_MCU: R210.1, U5.11 (IO7)
ENC1_A: C130.1, ENC1.8 (A), R130.2, U5.19 (IO15)
ENC1_B: C131.1, ENC1.10 (B), R131.2, U5.20 (IO16)
ENC1_SW: C132.1, ENC1.12 (E), R132.2, U5.21 (IO17)
ENC2_A: C230.1, ENC2.8 (A), R230.2, U5.17 (IO13)
ENC2_B: C231.1, ENC2.10 (B), R231.2, U5.18 (IO14)
ENC2_SW: C232.1, ENC2.12 (E), R232.2, U5.22 (IO18)
EN_RST: C18.1, R9.2, SW1.1 (AB), U5.45 (EN)
FB1: D14.1 (cathode), D16.2 (anode), Q11.3 (C), R102.2, R103.1, R111.1, U11.5 (FB)
FB2: D24.1 (cathode), D26.2 (anode), Q21.3 (C), R202.2, R203.1, R211.1, U21.5 (FB)
FB5: R5.2, R6.1, U3.5 (FB)
GND: C1.2, C2.2, C3.2, C4.2, C5.2, C6.2, C7.2, C8.2, C9.2, C10.2, C12.2, C13.2, C14.2, C15.2, C16.2, C17.2, C18.2, C20.2, C21.2, C22.2, C23.2, C24.2, C25.2, C26.2, C101.2, C102.2, C103.2, C105.2, C106.2, C107.2, C108.2, C109.2, C110.2, C111.2, C112.2, C113.2, C114.2, C115.2, C118.2, C119.2, C120.2, C130.2, C131.2, C132.2, C133.2, C201.2, C202.2, C203.2, C205.2, C206.2, C207.2, C208.2, C209.2, C210.2, C211.2, C212.2, C213.2, C214.2, C215.2, C218.2, C219.2, C220.2, C230.2, C231.2, C232.2, C233.2, D1.2 (A), D2.2, D13.1 (anode), D23.1 (anode), D102.2, D202.2, ENC1.6, ENC1.7, ENC1.9 (C), ENC1.11 (D), ENC2.6, ENC2.7, ENC2.9 (C), ENC2.11 (D)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
I2C_SCL: J3.3, R12.2, U1.7 (SCL), U5.13 (IO9), U12.5 (SCL), U22.5 (SCL)
I2C_SDA: J3.4, R11.2, U1.8 (SDA), U5.12 (IO8), U12.4 (SDA), U22.4 (SDA)
ISENS1: R115.1, U13.1
ISENS1_F: C116.1, R115.2, U7.3 (INA+)
ISENS2: R215.1, U23.1
ISENS2_F: C216.1, R215.2, U7.5 (INB+)
ISET1: R119.1, U5.15 (IO11)
ISET1_A: C118.1, R119.2, R120.1
ISET1_F: C119.1, R117.1, R120.2
ISET2: R219.1, U5.16 (IO12)
ISET2_A: C218.1, R219.2, R220.1
ISET2_F: C219.1, R217.1, R220.2
ISINK1_DRV: R105.1, U6.1 (OUTA)
ISINK1_E: Q11.2 (E), R104.1, U6.2 (INA-)
ISINK2_DRV: R205.1, U6.7 (OUTB)
ISINK2_E: Q21.2 (E), R204.1, U6.6 (INB-)
LAG1: C113.1, R111.2, R126.2
LAG2: C213.1, R211.2, R226.2
LED_CC1: R113.1, U5.25 (IO21)
LED_CC2: R213.1, U5.27 (IO47)
NTC1: C120.1, R124.2, TH11.1, U5.5 (IO1)
NTC2: C220.1, R224.2, TH21.1, U5.6 (IO2)
unnamed: D15.1 (cathode), R126.1
unnamed: D25.1 (cathode), R226.1
unnamed: D101.1, R112.2
unnamed: D102.1, R113.2
unnamed: D201.1, R212.2
unnamed: D202.1, R213.2
unnamed: D14.2 (anode), R116.2
unnamed: C117.2, R118.1
unnamed: C116.2, R125.1
unnamed: D24.2 (anode), R216.2
unnamed: C217.2, R218.1
unnamed: C216.2, R225.1
OUT1: C25.1, C114.1, D13.2 (cathode), J2.1, R101.2, R102.1, R121.2, U12.8 (Vbus), U12.9 (Vin-), U13.4 (-)
OUT1_B: C106.1, C107.1, C108.1, C109.1, L11.2, R101.1, U12.10 (Vin+), U13.3 (+)
OUT2: C26.1, C214.1, D23.2 (cathode), J2.3, R201.2, R202.1, R221.2, U22.8 (Vbus), U22.9 (Vin-), U23.4 (-)
OUT2_B: C206.1, C207.1, C208.1, C209.1, L21.2, R201.1, U22.10 (Vin+), U23.3 (+)
PD_ALERT: R13.2, U1.19 (ALERT), U5.14 (IO10)
PD_EN: R7.1, U1.16 (VBUS_EN_SNK)
PD_GATE: C19.2, Q1.4 (G), R3.2, R7.2
PWM1: R106.1, U5.8 (IO4)
PWM1_F: C110.1, R106.2, R107.1
PWM2: R206.1, U5.9 (IO5)
PWM2_F: C210.1, R206.2, R207.1
Q11_B: Q11.1 (B), R105.2
Q12_B: Q12.1 (B), R114.2
Q12_C: D101.2, Q12.3 (C)
Q13_D: Q13.3 (D), R121.1
Q14_B: Q14.1 (B), R122.2
Q21_B: Q21.1 (B), R205.2
Q22_B: Q22.1 (B), R214.2
Q22_C: D201.2, Q22.3 (C)
Q23_D: Q23.3 (D), R221.1
Q24_B: Q24.1 (B), R222.2
SW5: C11.2, L1.1, U3.8 (SW)
SW_CH1: C104.2, L11.1, U11.8 (SW)
SW_CH2: C204.2, L21.1, U21.8 (SW)
U1_VBUS_VS_DISCH: R1.2, U1.18 (VBUS_VS_DISCH)
U1_VREG_1V2: C2.1, U1.21 (VREG_1V2)
U1_VREG_2V7: C3.1, U1.23 (VREG_2V7)
U3_BOOT: C11.1, U3.7 (BOOT)
U3_EN: R4.2, U3.3 (EN)
U3_VCC: C20.1, U3.6 (VCC)
U11_BOOT: C104.1, U11.7 (BOOT)
U11_VCC: C105.1, U11.6 (VCC)
U21_BOOT: C204.1, U21.7 (BOOT)
U21_VCC: C205.1, U21.6 (VCC)
USB_DN: J1.19 (Dn2), J1.21 (Dn1), U2.3 (I/O2), U2.4 (I/O2), U5.23 (IO19)
USB_DP: J1.20 (Dp1), J1.22 (Dp2), U2.1 (I/O1), U2.6 (I/O1), U5.24 (IO20)
USB_SHIELD: C5.1, J1.13 (EH1), J1.14 (EH2), J1.27 (EH3), J1.28 (EH4), R2.1
V3V3: C15.1, C16.1, C17.1, C21.1, C22.1, C112.1, C115.1, C212.1, C215.1, D16.1 (cathode), D26.1 (cathode), J3.2, R9.1, R10.1, R11.1, R12.1, R13.1, R112.1, R124.1, R130.1, R131.1, R132.1, R133.1, R212.1, R224.1, R230.1, R231.1, R232.1, R233.1, TP4.1, U2.5 (VBUS), U4.5 (VOUT), U5.3 (3V3), U6.8 (VCC), U7.8 (VCC), U12.6 (VS), U13.6 (V+), U22.2 (A0), U22.6 (VS), U23.6 (V+)
V5: C12.1, C13.1, C14.1, C23.1, C24.1, L1.2, R5.1, R123.2, R223.2, TP3.1, U4.1 (VIN), U4.3 (EN)
VBUS: C1.1, C4.1, C19.1, D2.1, J1.16 (VBUS1), J1.25 (VBUS2), Q1.1 (S), Q1.2 (S), Q1.3 (S), R1.1, R3.1, TP1.1, U1.24 (VDD)
VIN: C6.1, C7.1, C8.1, C9.1, C10.1, C101.1, C102.1, C103.1, C201.1, C202.1, C203.1, D1.1 (C), Q1.5 (D), Q1.6 (D), Q1.7 (D), Q1.8 (D), R4.1, TP2.1, U3.2 (VIN), U11.2 (VIN), U21.2 (VIN)
VSET1: C111.1, R107.2, R108.1, U6.3 (INA+)
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
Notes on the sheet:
USB-C PD input (bottom)
logic supplies: 5 V buck + 3.3 V LDO (bottom)
MCU: ESP32-S3-MINI-1 (bottom, antenna at the +x edge)
other
output channels (bottom)
front panel (top)
